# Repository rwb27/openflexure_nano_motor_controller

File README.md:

# This repository has moved!
Please see https://gitlab.com/bath_open_instrumentation_group/sangaboard

# OpenFlexure Motor Controller (Sangaboard v0.2)

This aims to be a super-simple motor controller, based on an Arduino Nano and a couple of Darlington pair ICs.  It controls cheap 28BYJ-48 steppers, as used on the OpenFlexure microscope and stage.  It owes quite a bit to [Fergus Riche's motor board](https://github.com/fr293/motor_board), the hardware developed by [OpenScope](http://2015.igem.org/Team:Cambridge-JIC) and the Arduino-based motor controller used by a number of summer students working with Richard Bowman in Cambridge, particularly James Sharkey.  It is currently the motor board used by the [OpenFlexure Microscope](https://github.com/rwb27/openflexure_microscope/).

The repository contains three sets of files; the Arduino firmware in the ``arduino_code`` folder, a Python module in the ``openflexure_stage`` folder, and the PCB design in the ``pcb_design`` folder.

## Documentation
You can now see documentation at [Read the Docs](https://openflexure-stage.readthedocs.io/en/latest/index.html).

## Getting started

The first step is to make and populate the PCB.  You can get in touch with [WaterScope](http://www.waterscope.org/) to order one if they have stock, or alternatively have them made via [Kit Space](http://www.kitspace.org/) ([link to this project](https://kitspace.org/boards/github.com/rwb27/openflexure_nano_motor_controller/)).

Next you will need to download the Arduino sketch and upload it to the Arduino Nano.  You'll need some libraries, see the ``arduino_code`` folder's readme for that.

Lastly, you can control the stage using the ``openflexure_stage`` Python module.  This can be installed via pip, using ``pip install openflexure_stage``.  NB the master branch and the pip released version are currently not in sync, we're working to fix this.  If you want interactive control, you might want to check out the [OpenFlexure Microscope software](https://github.com/rwb27/openflexure_microscope_software/), which will run the stage together with the Raspberry Pi camera module.

## Credits

Firmware/Python code by Richard Bowman, University of Bath, PCB design & production by Sanga Valerian, STICLab.  Development of this board and software was funded by the EPSRC (EP/P029426/1), the Royal Commission for the Exhibition of 1851, and the University of Bath.

(c) The authors, 2017, released under CERN Open Hardware License (hardware designs) and GNU GPL v3.0 (software) 2017.

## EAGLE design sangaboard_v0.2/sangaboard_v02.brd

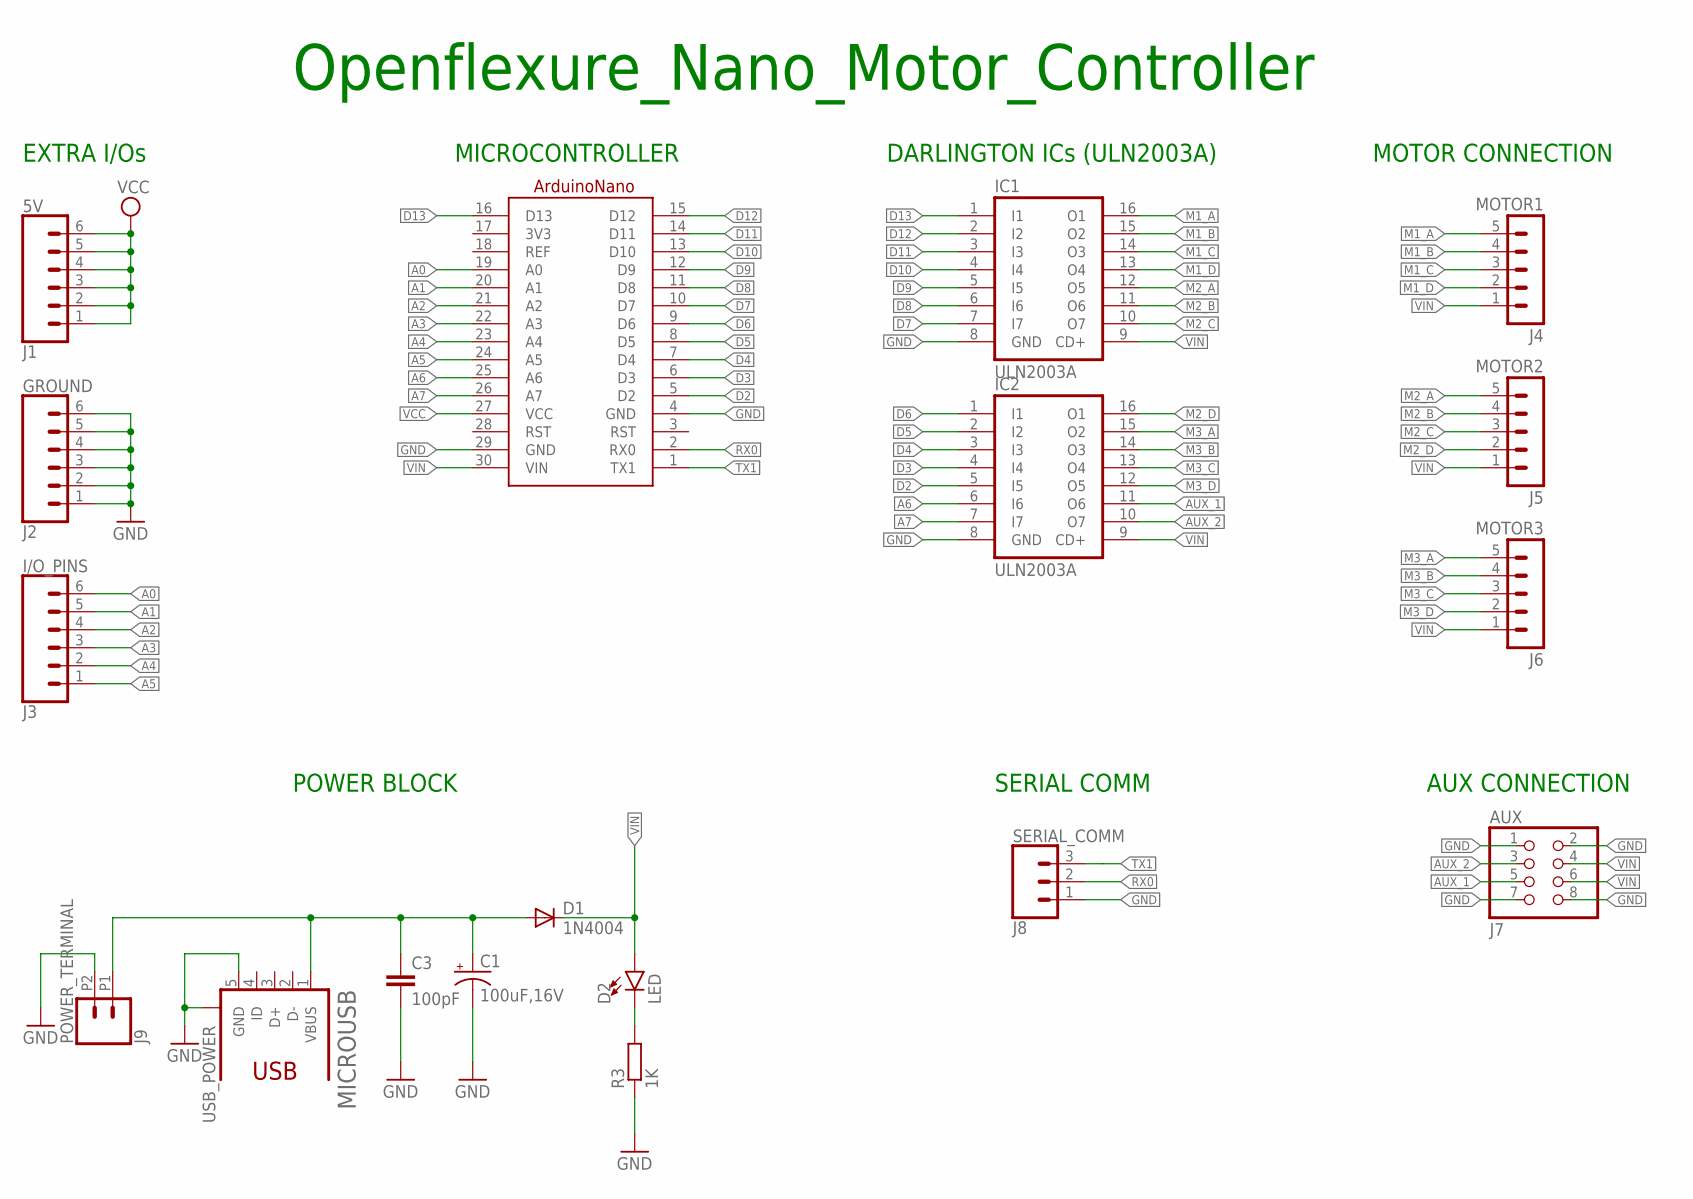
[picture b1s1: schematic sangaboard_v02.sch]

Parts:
5V: J1; 1X06_NO_SILK
A1: Arduino Nano; ARDUINONANO
AUX: J7; 2X04
C1: 100uF,16V; CPOL-RADIAL-2.5MM-6.5MM
C3: 100pF; CAP-PTH-2.54
D1: 1N4004; DO41-10
D2: LED; LED_3MM
GROUND: J2; 1X06_NO_SILK
I/O_PINS: J3; 1X06_NO_SILK
IC1, IC2: ULN2003A; DIL16
MICROUSB: USB_POWER; 1981584-1
MOTOR1: J4; MA05-1
MOTOR2: J5; MA05-1
MOTOR3: J6; MA05-1
POWER_TERMINAL: J9; 1X02_2.54_SCREWTERM
R3: 1K; 0207/10
SERIAL_COMM: J8; 1X03

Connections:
3V3: A1.17 (3V3)
A0: A1.19 (A0), I/O_PINS.6
A1: A1.20 (A1), I/O_PINS.5
A2: A1.21 (A2), I/O_PINS.4
A3: A1.22 (A3), I/O_PINS.3
A4: A1.23 (A4), I/O_PINS.2
A5: A1.24 (A5), I/O_PINS.1
A6: A1.25 (A6), IC2.6 (I6)
A7: A1.26 (A7), IC2.7 (I7)
AUX_1: AUX.5, IC2.11 (O6)
AUX_2: AUX.3, IC2.10 (O7)
D2: A1.5 (D2), IC2.5 (I5)
D3: A1.6 (D3), IC2.4 (I4)
D4: A1.7 (D4), IC2.3 (I3)
D5: A1.8 (D5), IC2.2 (I2)
D6: A1.9 (D6), IC2.1 (I1)
D7: A1.10 (D7), IC1.7 (I7)
D8: A1.11 (D8), IC1.6 (I6)
D9: A1.12 (D9), IC1.5 (I5)
D10: A1.13 (D10), IC1.4 (I4)
D11: A1.14 (D11), IC1.3 (I3)
D12: A1.15 (D12), IC1.2 (I2)
D13: A1.16 (D13), IC1.1 (I1)
GND: A1.4 (GND), A1.29 (GND), AUX.1, AUX.2, AUX.7, AUX.8, C1.2 (-), C3.2, GROUND.1, GROUND.2, GROUND.3, GROUND.4, GROUND.5, GROUND.6, IC1.8 (GND), IC2.8 (GND), MICROUSB.5 (GND), MICROUSB.S1, POWER_TERMINAL.P2 (2), R3.1, SERIAL_COMM.1
M1_A: IC1.16 (O1), MOTOR1.5
M1_B: IC1.15 (O2), MOTOR1.4
M1_C: IC1.14 (O3), MOTOR1.3
M1_D: IC1.13 (O4), MOTOR1.2
M2_A: IC1.12 (O5), MOTOR2.5
M2_B: IC1.11 (O6), MOTOR2.4
M2_C: IC1.10 (O7), MOTOR2.3
M2_D: IC2.16 (O1), MOTOR2.2
M3_A: IC2.15 (O2), MOTOR3.5
M3_B: IC2.14 (O3), MOTOR3.4
M3_C: IC2.13 (O4), MOTOR3.3
M3_D: IC2.12 (O5), MOTOR3.2
unnamed: D2.K (C), R3.2
unnamed: C1.1 (+), C3.1, D1.A, MICROUSB.1 (VBUS), POWER_TERMINAL.P1 (1)
REF: A1.18 (REF)
RX0: A1.2 (RX0), SERIAL_COMM.2
TX1: A1.1 (TX1), SERIAL_COMM.3
VCC: 5V.1, 5V.2, 5V.3, 5V.4, 5V.5, 5V.6, A1.27 (VCC)
VIN: A1.30 (VIN), AUX.4, AUX.6, D1.C, D2.A, IC1.9 (CD+), IC2.9 (CD+), MOTOR1.1, MOTOR2.1, MOTOR3.1

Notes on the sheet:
MICROCONTROLLER
EXTRA I/Os
DARLINGTON ICs (ULN2003A)
POWER BLOCK
MOTOR CONNECTION
AUX CONNECTION
SERIAL COMM
Openflexure_Nano_Motor_Controller

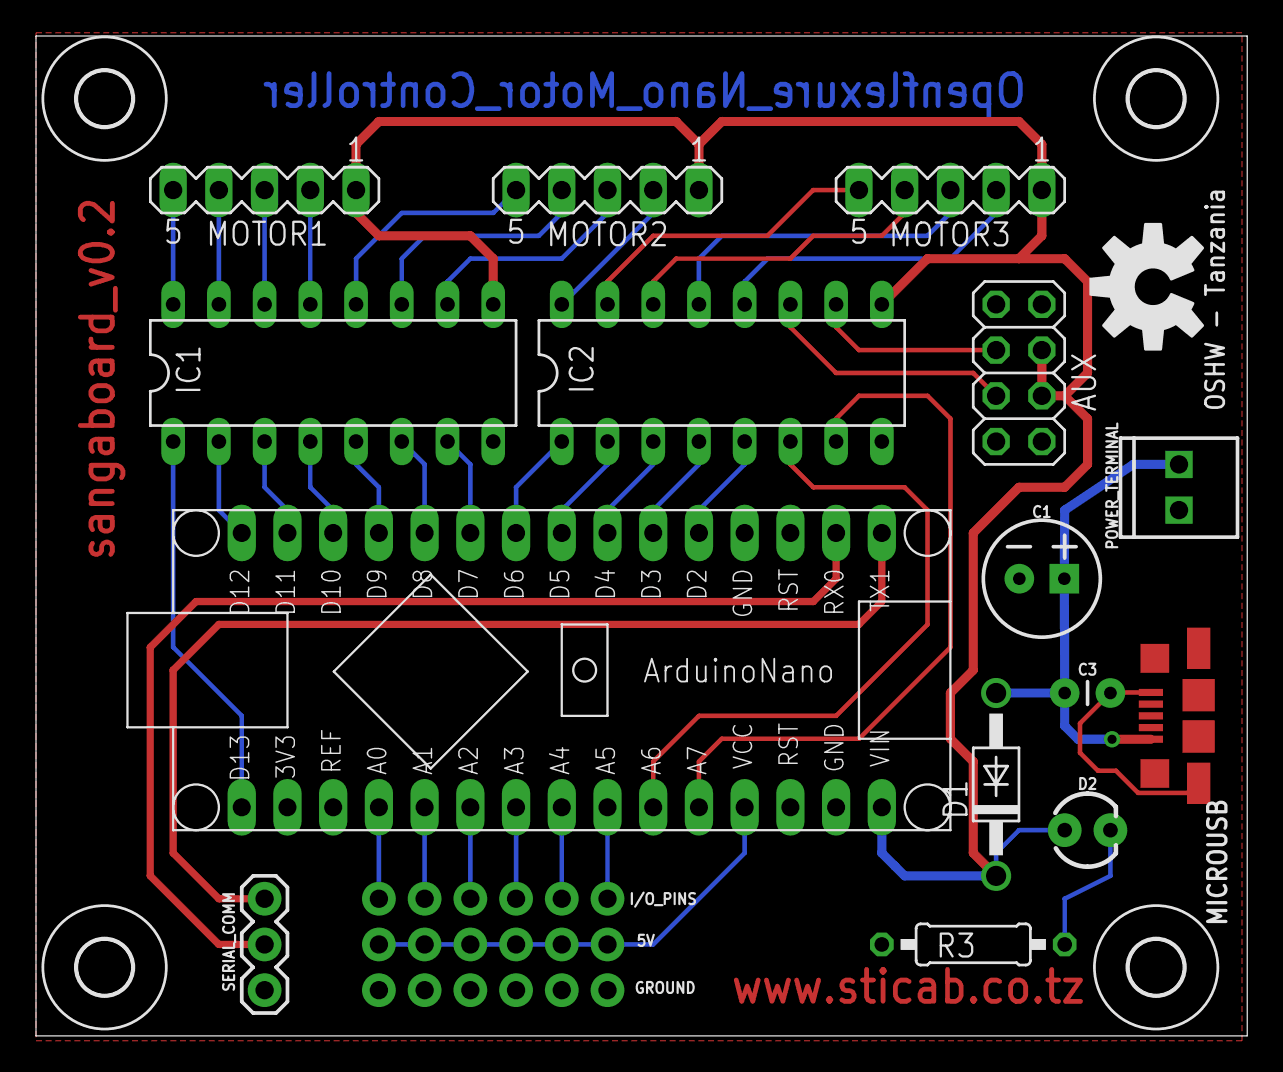
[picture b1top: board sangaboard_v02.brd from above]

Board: 2 copper layers, 67.3 x 55.5 mm, 23 parts (0 on the bottom side), 41 nets.

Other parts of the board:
U$1, U$2, U$3, U$4: 3,0
U$5: OSHW-LOGO-L

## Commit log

2017-06-18 :boom::camel: Added .gitattributes & .gitignore files
2017-06-19 Initial version of Arduino firmware and host Python code
    Currently only single-axis relative moves (rmx <steps> for x in x, y, z)
    work, though you can also get position (p?) and disable the steppers
    (release).
2017-06-19 Added a readme.
2017-06-26 Rename README.md.txt to README.md
2017-06-27 Add files via upload
    This PCB has been designed using Proteus Software.
2017-07-06 Credited prior art
    The PCB design was Valerian's, but my code was copy-pasted. Mostly from the arduino based motor controller I wrote myself, but from a few other places too; and it's important to acknowledge them...
2017-07-25 Working version with 3-axis move
2017-07-25 Changed test code to work as a library
    python code can now be safely imported.
2017-07-25 Settings now persist
    min_step_delay and ramp_time are now saved to EEPROM so they won't get
    lost on restart :)
2017-07-25 optimised and added persistence
    It now handles changing parameters on the fly, nice acceleration, and
    remembers where you left it after a power cycle!
2017-09-20 Added Valerian's Gerber files
2017-10-09 Added responses to parameter-setting commands
    changing ramp_time or min_step_delay is now acknowledged, for easier serial comms.
2017-11-20 Pasted in StepperF_alt
    I nastily hacked Fergus's mod of the Stepper library so I could make this work. TODO: make this neater!
2017-11-20 fixed type issue
    command_prefix takes a char** argument - now correctly declared as const.
2017-11-20 Revert "fixed type issue"
    This reverts commit c5333327fc0691ef8fdb637eeb7369b5fe947a9b.
2017-11-20 Adafruit TSL2591 Support
    Wrote some very basic functions to support light sensor use with a hacked SANGABOARD, on I2C. Should really break out the header pins for this properly - but for now, I've just soldered onto them fro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
2017-11-20 Made light sensor responses consistent
    light sensor responses are now consistent with other properties.
2017-11-20 removed colons from light sensor responses
2017-11-28 Updated python scripts from microscope repo (closes #4)
2017-11-28 Turned off TSL2591 support by default
    also made the help string refer to the light sensor only if it is enabled.
2017-12-11 Added support for ADS1115 light sensor
2017-12-11 turned off light sensor support by default
2017-12-11 updated authors/changes
2018-02-02 sangaboard_v0.2
    The new version of openflexure nano motor controller (sangaboard_v0.2) with the consideration of comments given on the first design.
    The design is made using Eagle.
2018-02-09 Fixed initial line bug
    The stage now correctly prints exactly one line when it starts.
2018-02-12 Turned Python code into a proper Python package
2018-02-12 Added linear scan functions
2018-02-12 Moved readme to RST for python package
2018-02-12 Sorted packaging info
2018-02-13 added egg-info to gitignore (though it seems not to work)
2018-03-07 Make compatible with kitspace.org
2018-03-08 Switch kitspace input to sangaboard
2018-03-09 Select parts for BOM
2018-03-27 Upated bugfix for query code if unexpected items appear in buffer between write and read
    Also:
    * Updated .gitignore for some linux stuff
    * Deleted stray .pyc file
    * Moved StepperF_alt files so automatically found by Arduino IDE
    * Updated arduino readme with a little info
2018-03-27 Modified Arduino code to allow more than 32767 steps in one go
2018-03-27 Improved help and light sensor support
    * All Adafruit libraries included as installed libraries with <>
    * Added instructions for installing adafruit libraries into ReadMe
    * Defined version string in .ino, as light sensors/help used no/wrong version number
    * Cleaned up help string formatting
    * Added help file termination line "--END--" to allow multiline read
    * Added function in python to print help: OpenFlexureStage.print_help()
2018-03-27 Partial support for light sensor in python, should add intensity QueriedProperty
2018-03-28 New OptionalModule class, LightSensor now an OptionalModule
    * Arduino now has method for listing installed modules
    * BasicSerialInstrument now warns when parsed_query has to make multiple reads to get match
    * New class OptionalModule for optional modules on serial instruments
    * QueriedProperty recognises OptionalModule objects and points BasicSerialInstrument calls to OptionalModule.parent
    * LightSensor class (sub class of OptionalModule) added
    * LightSensor class uses a combination of the code from my hacked light sensor
2018-06-06 Updated Bottom Layer
    Have updated the Aux header pin connection to Ground.
2018-07-05 corrected My Documents path on Windows
2018-07-05 Fix gerber path in kitspace.yaml
2018-07-05 Re-plot gerbers using oshpark cam job
    http://docs.oshpark.com/design-tools/eagle/generating-gerbers/
2018-07-05 Replace pcb_design with sangaboard
2018-07-06 Python3 compatibility
2018-07-06 future import for py2
2018-07-06 fix python3 print missed when merging
2018-07-06 remove impossible import in init
2018-07-06 remove debug print
2018-07-06 require future in setup.py
2018-07-11 fix micros() overflow in StepperF
    micros() overflows in ~ 70min, stepperF now checks for the overflow
    and adjusts the timing.
2018-07-11 fix micros() overflow in move_axes
    micros() overflows after ~70 min, this should handle the overflow correctly.
2018-07-12 basic endstop support
2018-07-19 Added documentation using Sphinx
2018-07-19 Fixed egg-info line in gitignore
2018-07-19 Updated docs and tidied up.
2018-07-19 Set up sphinxcontrib.apidoc
    need to pip install sphinxcontrib-apidoc
2018-07-20 Added requirements file
2018-07-20 More tidying of documentation & API docs in ToC
2018-07-20 arduino: support for endstops
2018-07-20 Improved syntax in "getting started"
2018-07-20 Improved error handling if board is set up badly
    The light sensor error message is now printed before the board ID, so that it causes an error. This could probably be done more elegantly, but it's ok for now.
    I've also added error handling to the constructor so it doesn't leave the port open in the event that we can't initialise the board.
2018-07-20 Updated versions and error checking
    The code will now raise an exception if the version is wrong in the firware version string, and point to the docs describing how to fix it.
2018-07-20 Added missing dependency on numpy
2018-07-20 arduino: endstop related fixes
    Prevents move_axes from changing its argument, several other endstop fixes.
2018-07-23 Endstops OptionalModule in openflexure_stage
    Endstops module can query endstop status, home axes, and set maxima for software
    endstops.
    Some minor changes to arduino code.
2018-07-25 documentation for Endstops
2018-07-25 Endstop description in docs
2018-07-25 endstops: support homing given axes
2018-07-25 endstops: remove unnecessary goto
2018-07-26 endstops: only respond after homing
    Removed some debug prints and added "done" print after homing so that the stage
    waits for homing to finish.
    Also fixes intermittent issue with software endstops resetting current position.
2018-07-26 endstops: fix returning hit endstop with min+soft
    Using compiler directives in the an else statement with no brackets meant that
    if min+soft endstops are used, hit endstop was not returned from move_axes.
2018-07-31 endstops: slower fine homing
2018-07-31 endstops: home axes argument format in help
2018-08-09 Add test mode
    Stage now has a test_mode property which is propagated to modules and the firmware.
    With test_mode on the stage will return more data about the homing procedure, will
    stay at 0 after homing and will not reset position when it hits an endstop.
    This property may be used in the future to report more data/change other behaviour
    as required for testing.
2018-08-23 Sangaboard v0.3 support
    Sangaboard v0.3 controller uses different pins to control the motors, this adds
    a define to select the version.
    The microcontroller on this board does not reset on new serial connections, so
    a version command was addded and openflexure_stage will query the firmware
    version. This means the new openflexure_stage is incompatible with older firmware.
2018-11-02 automatically select sangaboard version
2018-12-12 Added contributors.
2019-01-07 ignored dist folder
2019-01-08 Used automated version for GitHub link
    The download URL given for the package should link to the GitHub "archive" download for a tag, which should be v<x.y.z>. I've now used the auto-versioning function to do this, because the latest rele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
2019-02-22 Fixed mistake in arduino help string
2019-02-26 Add direct link to Kitspace page
2019-04-05 Board version identifies in help, custom booloader supported in firmware
2019-04-05 Hacked Arduino bootloader into one that identifies as the sangaboard
2019-04-05 added Bootloader README, and board descriptions
2019-04-05 Added Cern License file
2019-04-05 Cleaning up dead code
2019-04-05 Sill renaming change
2019-04-05 Rebranded the Arduino code.
2019-04-05 Split the python code into a stage class and a Sangaboard class
2019-04-30 Delete everything that was put into new repos
    New repos are on GitLab under Bath Open Instrumentation Group
    * A repo was made for the Sangaboard, and it's firmware and bootloader
    * A repo was made for a python sangboard module (pySangaboard)
    Both modules had some BGFing of the history to make it somehwat sane
    I did not BFG the history of this!!
    What is left now needs merging into the OpenFlexure microscope client

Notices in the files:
parts and their libraries:
SparkFun-Connectors: Licensing: Creative Commons ShareAlike 4.0 International - https://creativecommons.org/licenses/by-sa/4.0
